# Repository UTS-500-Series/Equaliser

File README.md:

# UTS Mini Mixing Desk — Equaliser

A 500-series equaliser module for the UTS Mini Mixing Desk.

## Licence

Copyright 2026 the UTS 500 Series team.

This source describes Open Hardware and is licensed under the CERN-OHL-S v2.

You may redistribute and modify this source and make products using it under
the terms of the [CERN-OHL-S v2](https://ohwr.org/cern_ohl_s_v2.txt).

This source is distributed WITHOUT ANY EXPRESS OR IMPLIED WARRANTY, INCLUDING
OF MERCHANTABILITY, SATISFACTORY QUALITY AND FITNESS FOR A PARTICULAR PURPOSE.
Please see the CERN-OHL-S v2 for applicable conditions.

Source location: https://github.com/UTS-500-Series/Equaliser

As per CERN-OHL-S v2 section 4, should You produce hardware based on this
source, You must where practicable maintain the Source Location visible on the
external case of the equaliser module or other products you make
using this source.

The full licence text is in [LICENSE](LICENSE).

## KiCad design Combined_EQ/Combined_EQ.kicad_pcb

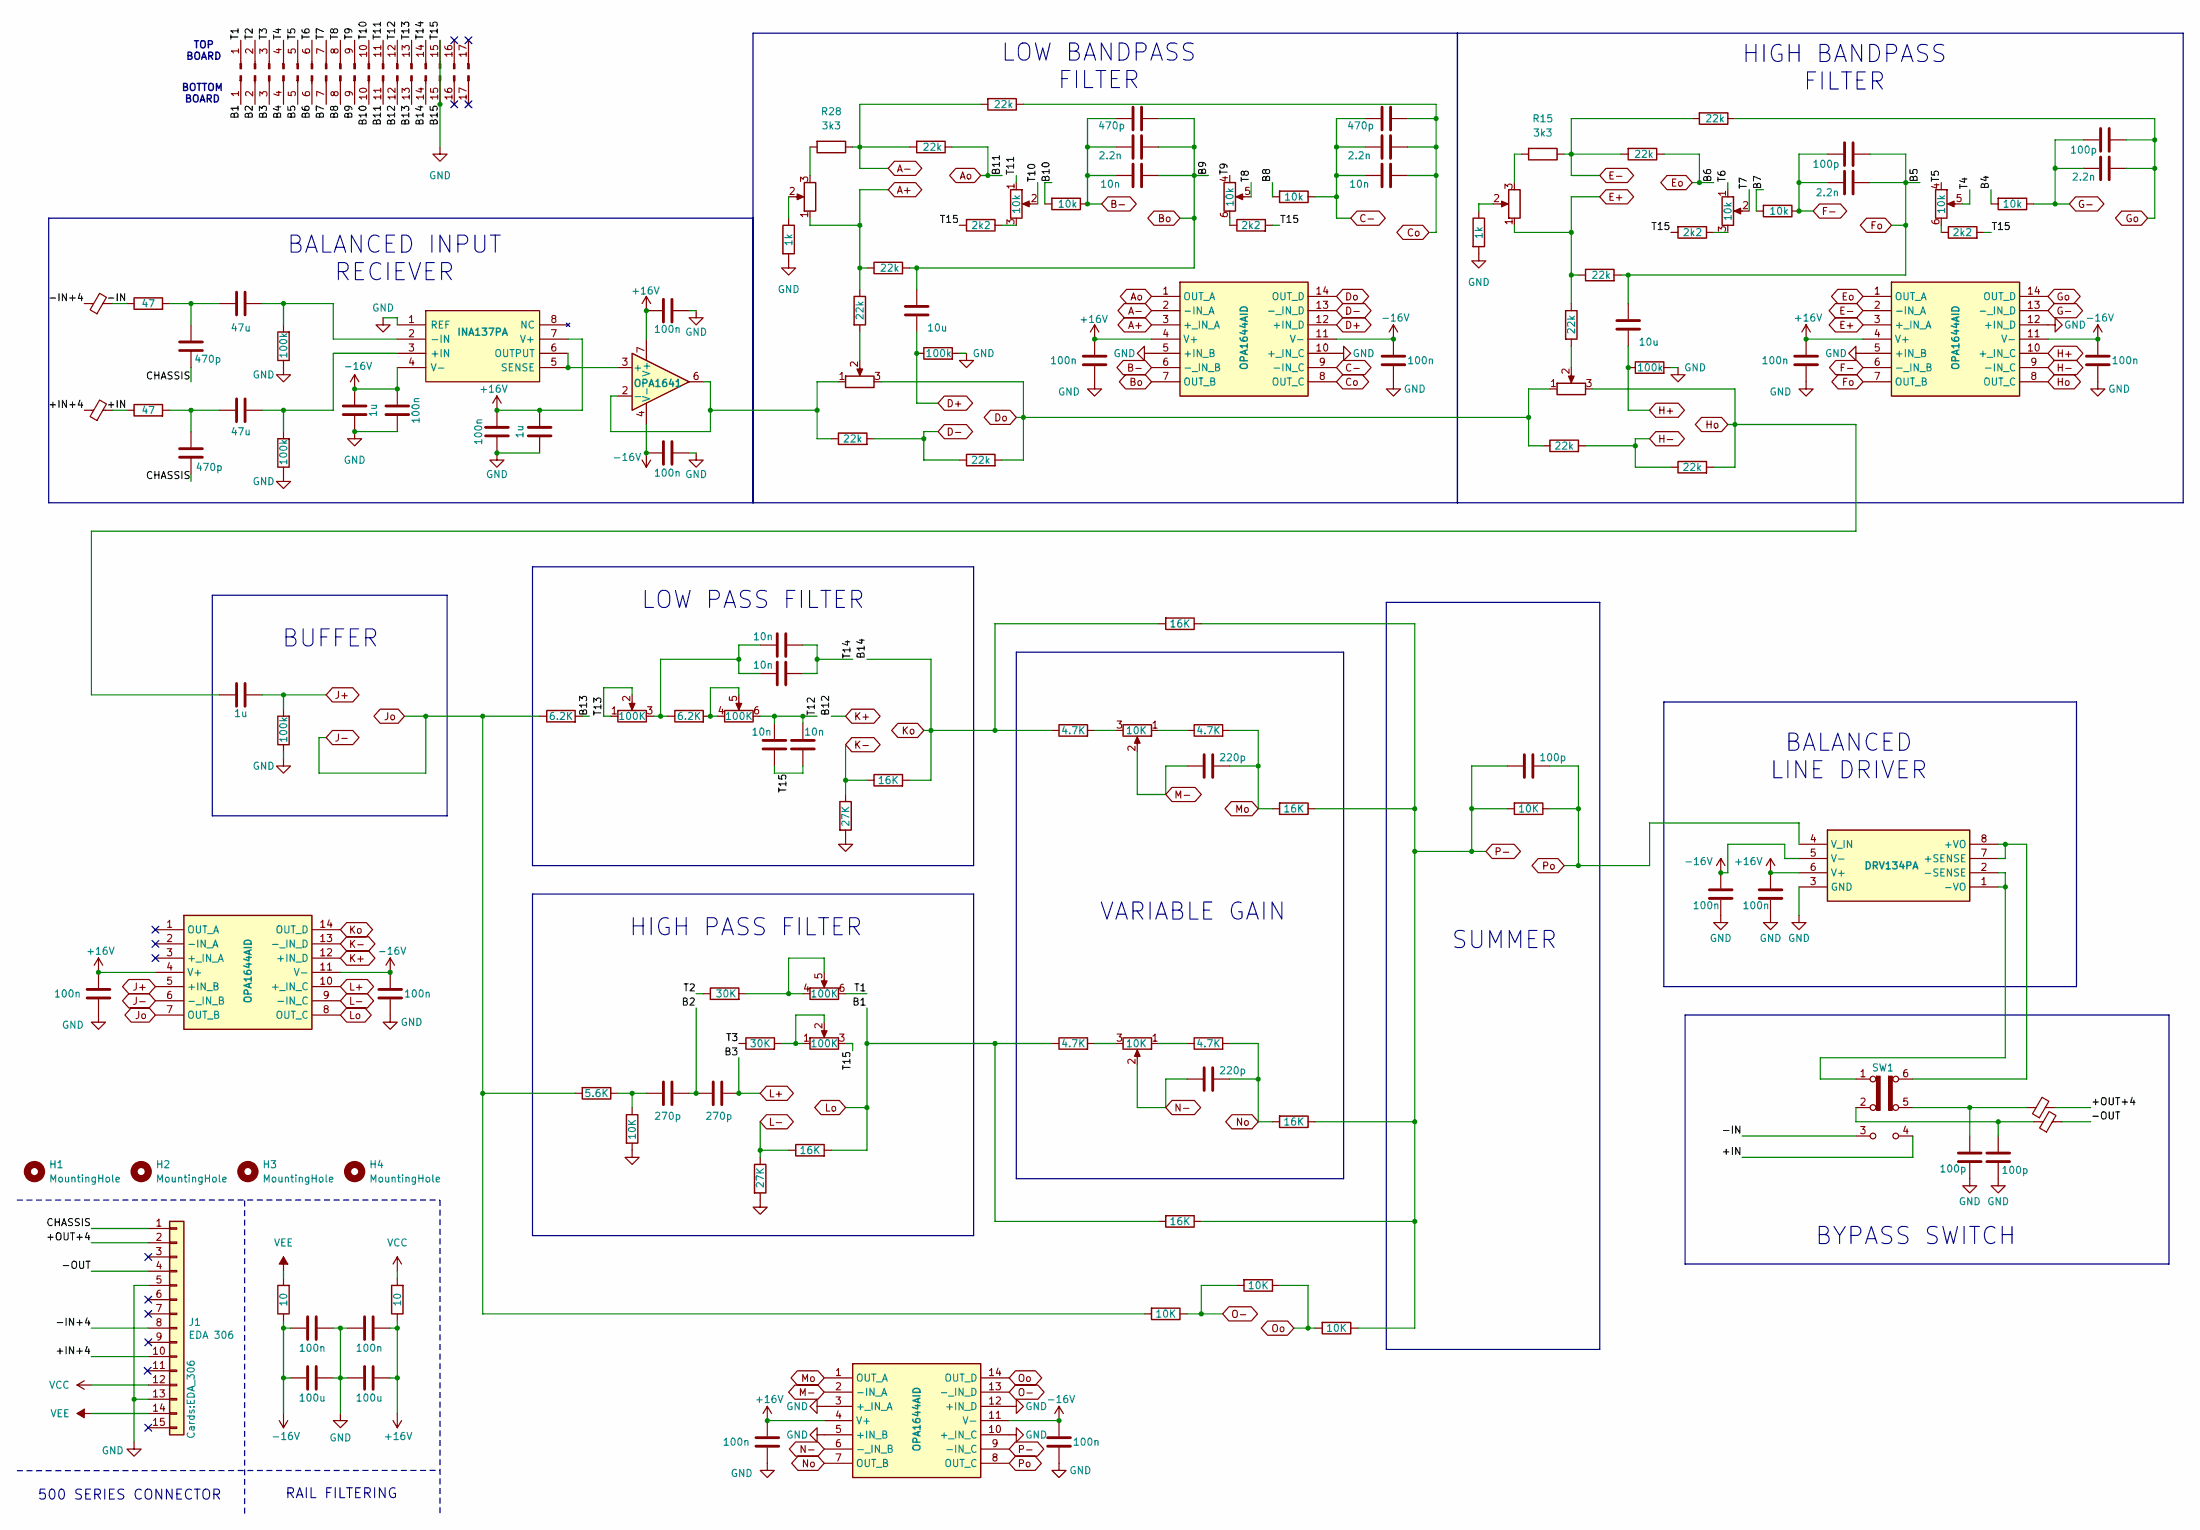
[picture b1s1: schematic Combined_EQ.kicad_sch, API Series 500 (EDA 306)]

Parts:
C1, C5, C9, C40: 470p; C_Disc_D5.0mm_W2.5mm_P5.00mm
C2, C7: 10u; C_Rect_L4.0mm_W2.5mm_P2.50mm
C3, C6, C39, C42: 2.2n; C_Disc_D5.0mm_W2.5mm_P5.00mm
C4, C10: 47u; C_Radial_D8.0mm_H7.0mm_P3.50mm
C8, C24, C27, C43, C46, C47: 10n; C_Disc_D5.0mm_W2.5mm_P5.00mm
C11, C12, C23: 1u; C_Disc_D5.0mm_W2.5mm_P5.00mm
C13, C14, C15, C16, C17, C19, C21, C22, C30, C31, C32, C34, C37, C38, C45, C48: 100n; C_Disc_D5.0mm_W2.5mm_P5.00mm
C18, C20: 100u; C_Disc_D5.0mm_W2.5mm_P5.00mm
C25, C26: 270p; C_Disc_D5.0mm_W2.5mm_P5.00mm
C28, C35, C36, C41, C44: 100p; C_Disc_D5.0mm_W2.5mm_P5.00mm
C29, C33: 220p; C_Disc_D5.0mm_W2.5mm_P5.00mm
FB1, FB2, FB3, FB4: 2944666671; LairdTech_28C0236-0JW-10
H1, H2, H3, H4: MountingHole; MountingHole_3.2mm_M3
IC1: INA137PA; DIP794W53P254L959H508Q8N; Manufacturer_Part_Number INA137PA; Mouser Part Number 595-INA137PA
IC2, IC3, IC4, IC8: OPA1644AID; SOIC127P600X175-14N; Manufacturer_Part_Number OPA1644AID; Mouser Part Number 595-OPA1644AID
IC6: DRV134PA; DIP794W53P254L959H508Q8N; Manufacturer_Part_Number DRV134PA; Mouser Part Number 595-DRV134PA
J1: EDA 306; EDA_306
J2, J3: Conn_01x17_Pin; PinHeader_1x17_P2.54mm_Vertical
R1, R3: 47; R_Axial_DIN0207_L6.3mm_D2.5mm_P10.16mm_Horizontal
R2, R4, R7, R20, R33: 100k; R_Axial_DIN0207_L6.3mm_D2.5mm_P10.16mm_Horizontal
R5, R6: 10; R_Axial_DIN0207_L6.3mm_D2.5mm_P10.16mm_Horizontal
R8, R9: 6.2K; R_Axial_DIN0207_L6.3mm_D2.5mm_P10.16mm_Horizontal
R10, R41: 27K; R_Axial_DIN0207_L6.3mm_D2.5mm_P10.16mm_Horizontal
R11, R43, R51, R52, R53, R54: 16K; R_Axial_DIN0207_L6.3mm_D2.5mm_P10.16mm_Horizontal
R12: 5.6K; R_Axial_DIN0207_L6.3mm_D2.5mm_P10.16mm_Horizontal
R13, R44, R49, R50, R55: 10K; R_Axial_DIN0207_L6.3mm_D2.5mm_P10.16mm_Horizontal
R14, R27: 1k; R_Axial_DIN0207_L6.3mm_D2.5mm_P10.16mm_Horizontal
R15, R28: 3k3; R_Axial_DIN0207_L6.3mm_D2.5mm_P10.16mm_Horizontal
R16, R17, R18, R19, R22, R23, R29, R30, R31, R32, R35, R39: 22k; R_Axial_DIN0207_L6.3mm_D2.5mm_P10.16mm_Horizontal
R21, R25, R34, R37: 2k2; R_Axial_DIN0207_L6.3mm_D2.5mm_P10.16mm_Horizontal
R24, R26, R36, R38: 10k; R_Axial_DIN0207_L6.3mm_D2.5mm_P10.16mm_Horizontal
R40, R42: 30K; R_Axial_DIN0207_L6.3mm_D2.5mm_P10.16mm_Horizontal
R45, R46, R47, R48: 4.7K; R_Axial_DIN0207_L6.3mm_D2.5mm_P10.16mm_Horizontal
RV1, RV4: 100K; Potentiometer_Alps_RK097_Dual_Horizontal
RV2, RV5, RV7, RV8: 10k; Potentiometer_Alps_RK097_Single_Horizontal
RV3, RV10: 10K; Potentiometer_Alps_RK097_Single_Horizontal
RV6, RV9: 10k; Potentiometer_Alps_RK097_Dual_Horizontal
SW1: SW_Slide_DPDT; SW_CK_JS202011CQN_DPDT_Straight
U1: OPA1641; SOIC127P600X175-8N

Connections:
+16V: C12.2, C13.2, C15.2, C19.2, C20.2, C21.2, C30.2, C34.1, C38.2, C45.2, IC1.7 (V+), IC2.4 (V+), IC3.4 (V+), IC4.4 (V+), IC6.6 (V+), IC8.4 (V+), R6.1, U1.7 (V+)
-16V: C11.2, C14.2, C16.2, C17.1, C18.1, C22.2, C31.2, C32.1, C37.2, C48.2, IC1.4 (V-), IC2.11 (V-), IC3.11 (V-), IC4.11 (V-), IC6.5 (V-), IC8.11 (V-), R5.1, U1.4 (V-)
/+IN: FB2.2, R3.1, SW1.4 (A)
/+IN+4: FB2.1, J1.10
/+OUT+4: FB3.2, J1.2
/-IN: FB1.2, R1.1, SW1.3 (C)
/-IN+4: FB1.1, J1.8
/-OUT: FB4.2, J1.4
/B2: C25.2, C26.1, J3.2
/B4: J3.4, R26.2
/B7: J3.7, R24.2
/B8: J3.8, R38.2
/B10: J3.10, R36.2
/B13: J3.13, R8.2
/CHASSIS: C1.2, C5.2, J1.1
/T1: J2.1, RV4.6
/T2: J2.2, R40.1
/T3: J2.3, R42.1
/T4: J2.4, RV6.5
/T5: J2.5, RV6.4
/T6: J2.6, RV6.1
/T7: J2.7, RV6.2
/T8: J2.8, RV9.5
/T9: J2.9, RV9.4
/T10: J2.10, RV9.2
/T11: J2.11, RV9.1
/T12: C46.1, C47.1, J2.12, RV1.6
/T13: J2.13, RV1.1, RV1.2
/T14: C24.1, C27.1, J2.14
A+: IC3.3 (+_IN_A), R30.1, R31.1, RV7.1
A-: IC3.2 (-IN_A), R28.1, R32.2, R35.2
Ao: IC3.1 (OUT_A), J3.11, R32.1
B-: C8.1, C39.1, C40.1, IC3.6 (-_IN_B), R36.1
Bo: C7.2, C8.2, C39.2, C40.2, IC3.7 (OUT_B), J3.9, R31.2
C-: C9.1, C42.1, C43.1, IC3.9 (-IN_C), R38.1
Co: C9.2, C42.2, C43.2, IC3.8 (OUT_C), R35.1
D+: C7.1, IC3.12 (+IN_D), R33.1
D-: IC3.13 (-_IN_D), R29.2, R39.1
Do: IC3.14 (OUT_D), R16.1, R39.2, RV5.1, RV8.3
E+: IC2.3 (+_IN_A), R17.1, R18.1, RV2.1
E-: IC2.2 (-IN_A), R15.1, R19.2, R23.2
Eo: IC2.1 (OUT_A), J3.6, R19.1
F-: C3.1, C41.1, IC2.6 (-_IN_B), R24.1
Fo: C2.2, C3.2, C41.2, IC2.7 (OUT_B), J3.5, R18.2
G-: C6.1, C44.1, IC2.13 (-_IN_D), R26.1
GND: C11.1, C12.1, C13.1, C14.1, C15.1, C16.1, C17.2, C18.2, C19.1, C20.1, C21.1, C22.1, C30.1, C31.1, C32.2, C34.2, C35.2, C36.1, C37.1, C38.1, C45.1, C46.2, C47.2, C48.1, IC1.1 (REF), IC2.5 (+IN_B), IC2.12 (+IN_D), IC3.5 (+IN_B), IC3.10 (+_IN_C), IC6.3 (GND), IC8.3 (+_IN_A), IC8.5 (+IN_B), IC8.10 (+_IN_C), IC8.12 (+IN_D), J1.5, J1.13, J2.15, J3.15, R2.1, R4.1, R7.1, R10.2, R13.2, R14.2, R20.2, R21.2, R25.2, R27.2, R33.2, R34.2, R37.2, R41.2, RV4.3
Go: C6.2, C44.2, IC2.14 (OUT_D), R23.1
H+: C2.1, IC2.10 (+_IN_C), R20.1
H-: IC2.9 (-IN_C), R16.2, R22.1
Ho: C23.1, IC2.8 (OUT_C), R22.2, RV5.3
J+: C23.2, IC4.5 (+IN_B), R7.2
J-: IC4.6 (-_IN_B), IC4.7 (OUT_B), R8.1, R12.2, R44.2
K+: IC4.12 (+IN_D), J3.12
K-: IC4.13 (-_IN_D), R10.1, R11.1
Ko: IC4.14 (OUT_D), J3.14, R11.2, R45.1, R54.2
L+: C26.2, IC4.10 (+_IN_C), J3.3
L-: IC4.9 (-IN_C), R41.1, R43.1
Lo: IC4.8 (OUT_C), J3.1, R43.2, R47.1, R53.2
M-: C29.1, IC8.2 (-IN_A), RV3.2
Mo: C29.2, IC8.1 (OUT_A), R46.2, R52.2
N-: C33.1, IC8.6 (-_IN_B), RV10.2
unnamed: C1.1, C4.1, R1.2
unnamed: C5.1, C10.1, R3.2
unnamed: C24.2, C27.2, R9.1, RV1.3
unnamed: C25.1, R12.1, R13.1
unnamed: C35.1, FB4.1, SW1.2 (B)
unnamed: C36.2, FB3.1, SW1.5 (B)
unnamed: C10.2, IC1.3 (+IN), R4.2
unnamed: C4.2, IC1.2 (-IN), R2.2
unnamed: IC1.5 (SENSE), IC1.6 (OUTPUT), U1.3 (+)
unnamed: IC6.7 (+SENSE), IC6.8 (+VO), SW1.6 (C)
unnamed: IC6.1 (-VO), IC6.2 (-SENSE), SW1.1 (A)
unnamed: R9.2, RV1.4, RV1.5
unnamed: R14.1, RV2.2
unnamed: R15.2, RV2.3
unnamed: R17.2, RV5.2
unnamed: R21.1, RV6.3
unnamed: R25.1, RV6.6
unnamed: R27.1, RV7.2
unnamed: R28.2, RV7.3
unnamed: R30.2, RV8.2
unnamed: R34.1, RV9.3
unnamed: R37.1, RV9.6
unnamed: R40.2, RV4.4, RV4.5
unnamed: R42.2, RV4.1, RV4.2
unnamed: R45.2, RV3.3
unnamed: R46.1, RV3.1
unnamed: R47.2, RV10.3
unnamed: R48.1, RV10.1
unnamed: R29.1, RV8.1, U1.2 (-), U1.6
No: C33.2, IC8.7 (OUT_B), R48.2, R51.2
O-: IC8.13 (-_IN_D), R44.1, R49.2
Oo: IC8.14 (OUT_D), R49.1, R50.2
P-: C28.1, IC8.9 (-IN_C), R50.1, R51.1, R52.1, R53.1, R54.1, R55.2
Po: C28.2, IC6.4 (V_IN), IC8.8 (OUT_C), R55.1
VCC: J1.12, R6.2
VEE: J1.14, R5.2

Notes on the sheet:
BALANCED LINE DRIVER
VARIABLE GAIN
BOTTOM BOARD
SUMMER
BYPASS SWITCH
BUFFER
HIGH PASS FILTER
500 SERIES CONNECTOR
RAIL FILTERING
LOW PASS FILTER
TOP BOARD
LOW BANDPASS FILTER
BALANCED INPUT RECIEVER
HIGH BANDPASS FILTER

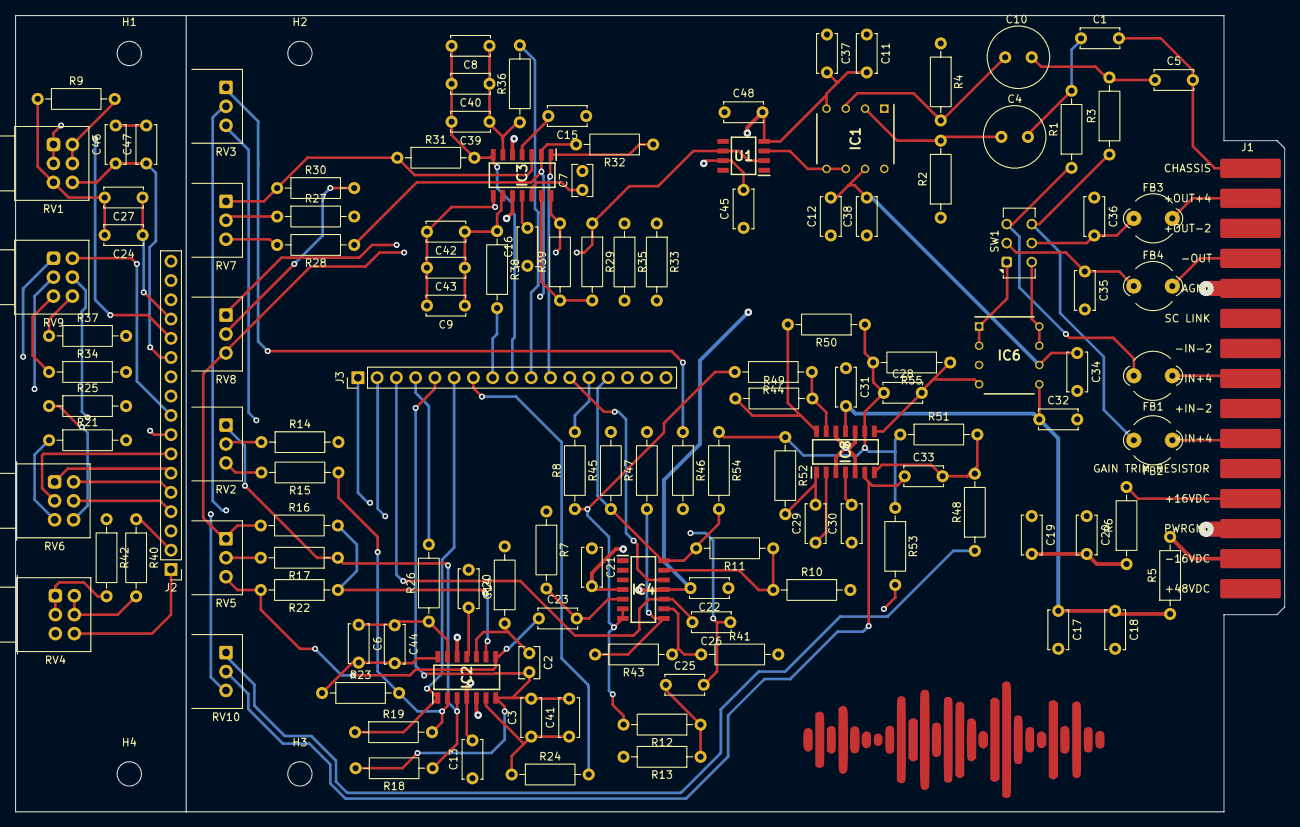
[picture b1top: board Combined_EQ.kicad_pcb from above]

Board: 4 copper layers, 167.3 x 105.0 mm, 132 parts (0 on the bottom side), 97 nets.

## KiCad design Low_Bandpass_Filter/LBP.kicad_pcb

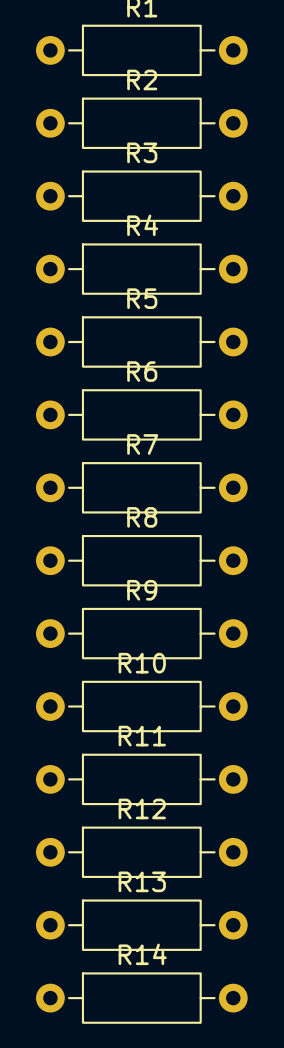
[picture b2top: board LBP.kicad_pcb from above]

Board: 2 copper layers, 15 parts (0 on the bottom side), 4 nets, no tracks yet.

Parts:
R1: 1k; R_Axial_DIN0207_L6.3mm_D2.5mm_P10.16mm_Horizontal
R2: 3k3; R_Axial_DIN0207_L6.3mm_D2.5mm_P10.16mm_Horizontal
R3, R4, R5, R6, R12, R13: 22k; R_Axial_DIN0207_L6.3mm_D2.5mm_P10.16mm_Horizontal
R7, R8: 10k; R_Axial_DIN0207_L6.3mm_D2.5mm_P10.16mm_Horizontal
R9, R10: 2k2; R_Axial_DIN0207_L6.3mm_D2.5mm_P10.16mm_Horizontal
R11: 100k; R_Axial_DIN0207_L6.3mm_D2.5mm_P10.16mm_Horizontal
R14: 100; R_Axial_DIN0207_L6.3mm_D2.5mm_P10.16mm_Horizontal
U1: OPA1641; SOP65P640X120-14N

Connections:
GND: R1.2, R11.2
unnamed: R5.1, R6.1
unnamed: R2.1, R3.2, R4.2
unnamed: R12.1, R13.2
